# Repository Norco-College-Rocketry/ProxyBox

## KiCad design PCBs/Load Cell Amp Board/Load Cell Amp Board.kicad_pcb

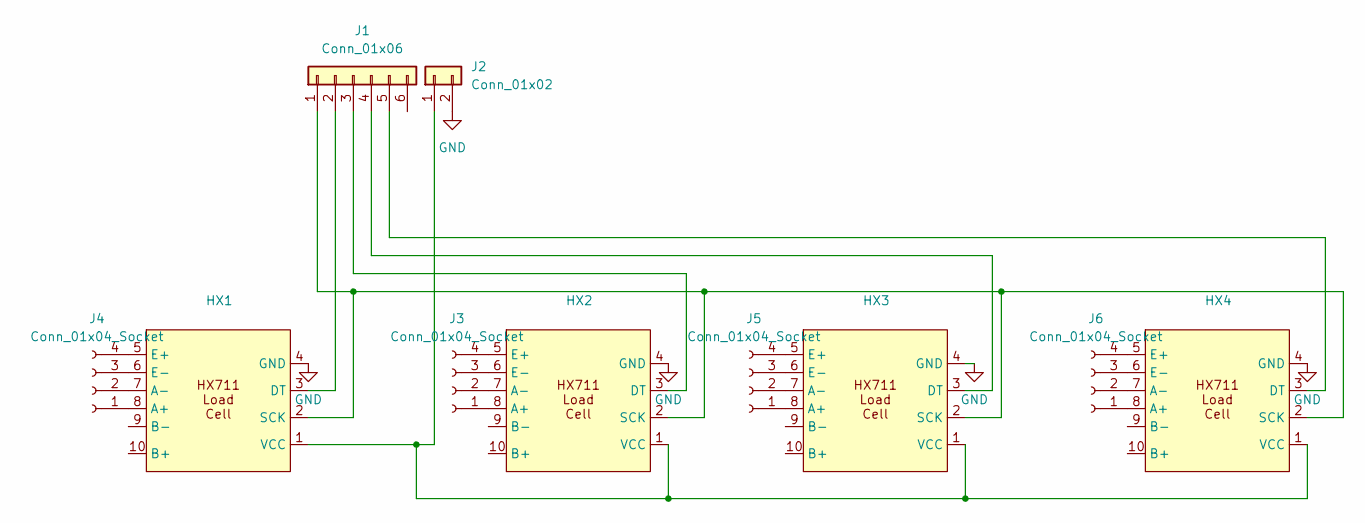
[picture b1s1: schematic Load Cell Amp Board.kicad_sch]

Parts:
HX1, HX2, HX3, HX4: HX711 Load Cell Amp Board
J1: Conn_01x06; Molex_Micro-Fit_3.0_43650-0619_1x06_P3.00mm_Vertical
J2: Conn_01x02; JST_XH_B2B-XH-A_1x02_P2.50mm_Vertical
J3, J4, J5, J6: Conn_01x04_Socket; Molex_Micro-Fit_3.0_43045-0412_2x02_P3.00mm_Vertical

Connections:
GND: HX1.4 (GND), HX2.4 (GND), HX3.4 (GND), HX4.4 (GND), J2.2
unnamed: HX1.8 (A+), J4.1
unnamed: HX1.7 (A-), J4.2
unnamed: HX1.3 (DT), J1.2
unnamed: HX1.5 (E+), J4.4
unnamed: HX1.6 (E-), J4.3
unnamed: HX1.2 (SCK), HX2.2 (SCK), HX3.2 (SCK), HX4.2 (SCK), J1.1
unnamed: HX1.1 (VCC), HX2.1 (VCC), HX3.1 (VCC), HX4.1 (VCC), J2.1
unnamed: HX2.8 (A+), J3.1
unnamed: HX2.7 (A-), J3.2
unnamed: HX2.3 (DT), J1.3
unnamed: HX2.5 (E+), J3.4
unnamed: HX2.6 (E-), J3.3
unnamed: HX3.8 (A+), J5.1
unnamed: HX3.7 (A-), J5.2
unnamed: HX3.3 (DT), J1.4
unnamed: HX3.5 (E+), J5.4
unnamed: HX3.6 (E-), J5.3
unnamed: HX4.8 (A+), J6.1
unnamed: HX4.7 (A-), J6.2
unnamed: HX4.3 (DT), J1.5
unnamed: HX4.5 (E+), J6.4
unnamed: HX4.6 (E-), J6.3

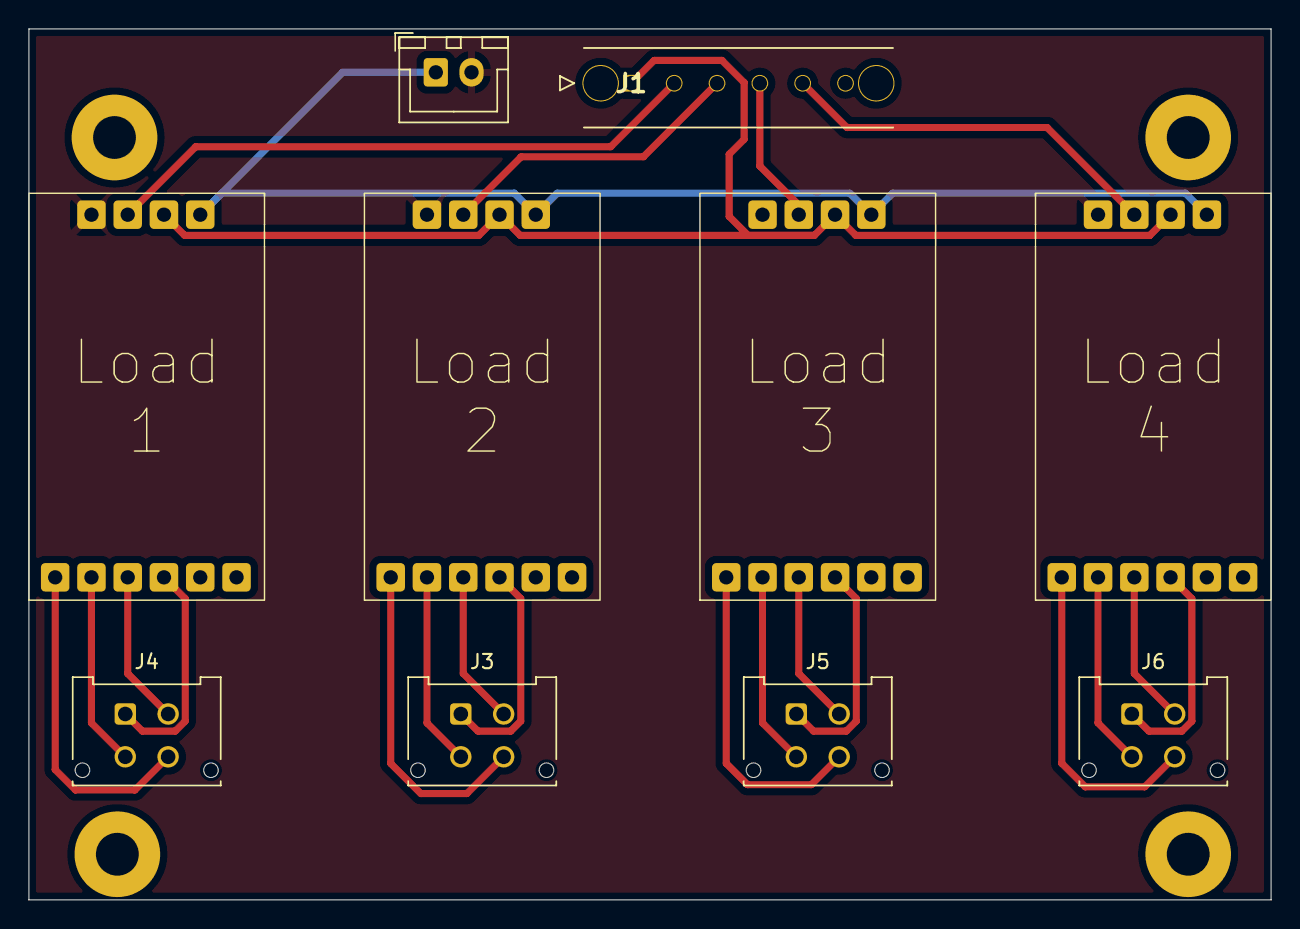
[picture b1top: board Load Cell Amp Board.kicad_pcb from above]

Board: 2 copper layers, 87.0 x 61.0 mm, 10 parts (0 on the bottom side), 23 nets.

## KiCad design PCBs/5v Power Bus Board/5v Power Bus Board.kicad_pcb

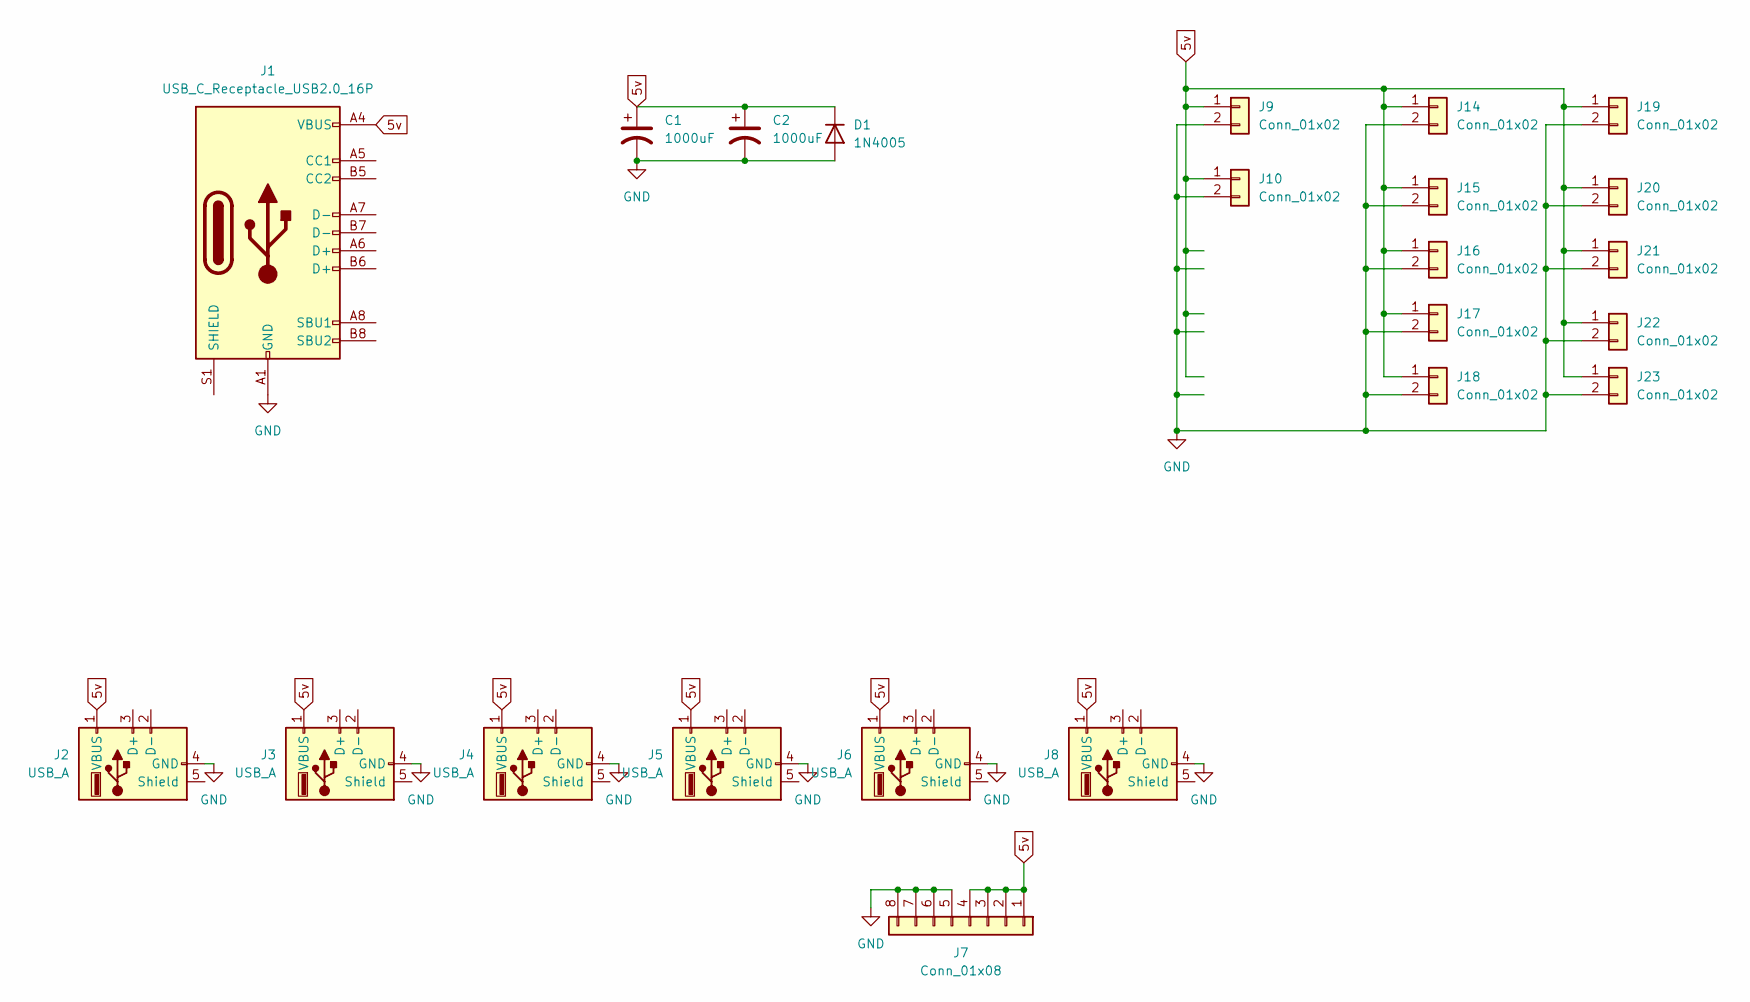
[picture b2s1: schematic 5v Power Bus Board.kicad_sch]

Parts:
C1, C2: 1000uF; CP_Radial_D12.5mm_P5.00mm
D1: 1N4005; D_DO-41_SOD81_P10.16mm_Horizontal
J1: USB_C_Receptacle_USB2.0_16P; USB_C_Receptacle_GCT_USB4105-xx-A_16P_TopMnt_Horizontal
J2, J3, J4, J5, J6, J8: USB_A; USB1125GFB
J7: Conn_01x08; TerminalBlock_4Ucon_1x08_P3.50mm_Horizontal
J9, J10, J14, J15, J16, J17, J18, J19, J20, J21, J22, J23: Conn_01x02; JST_XH_B2B-XH-A_1x02_P2.50mm_Vertical

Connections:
5v: C1.1, C2.1, D1.1 (K), J1.A4 (VBUS), J1.A9 (VBUS), J1.B4 (VBUS), J1.B9 (VBUS), J2.1 (VBUS), J3.1 (VBUS), J4.1 (VBUS), J5.1 (VBUS), J6.1 (VBUS), J7.1, J7.2, J7.3, J7.4, J8.1 (VBUS), J9.1, J10.1, J14.1, J15.1, J16.1, J17.1, J18.1, J19.1, J20.1, J21.1, J22.1, J23.1
GND: C1.2, C2.2, D1.2 (A), J1.A1 (GND), J1.A12 (GND), J1.B1 (GND), J1.B12 (GND), J2.4 (GND), J3.4 (GND), J4.4 (GND), J5.4 (GND), J6.4 (GND), J7.5, J7.6, J7.7, J7.8, J8.4 (GND), J9.2, J10.2, J14.2, J15.2, J16.2, J17.2, J18.2, J19.2, J20.2, J21.2, J22.2, J23.2

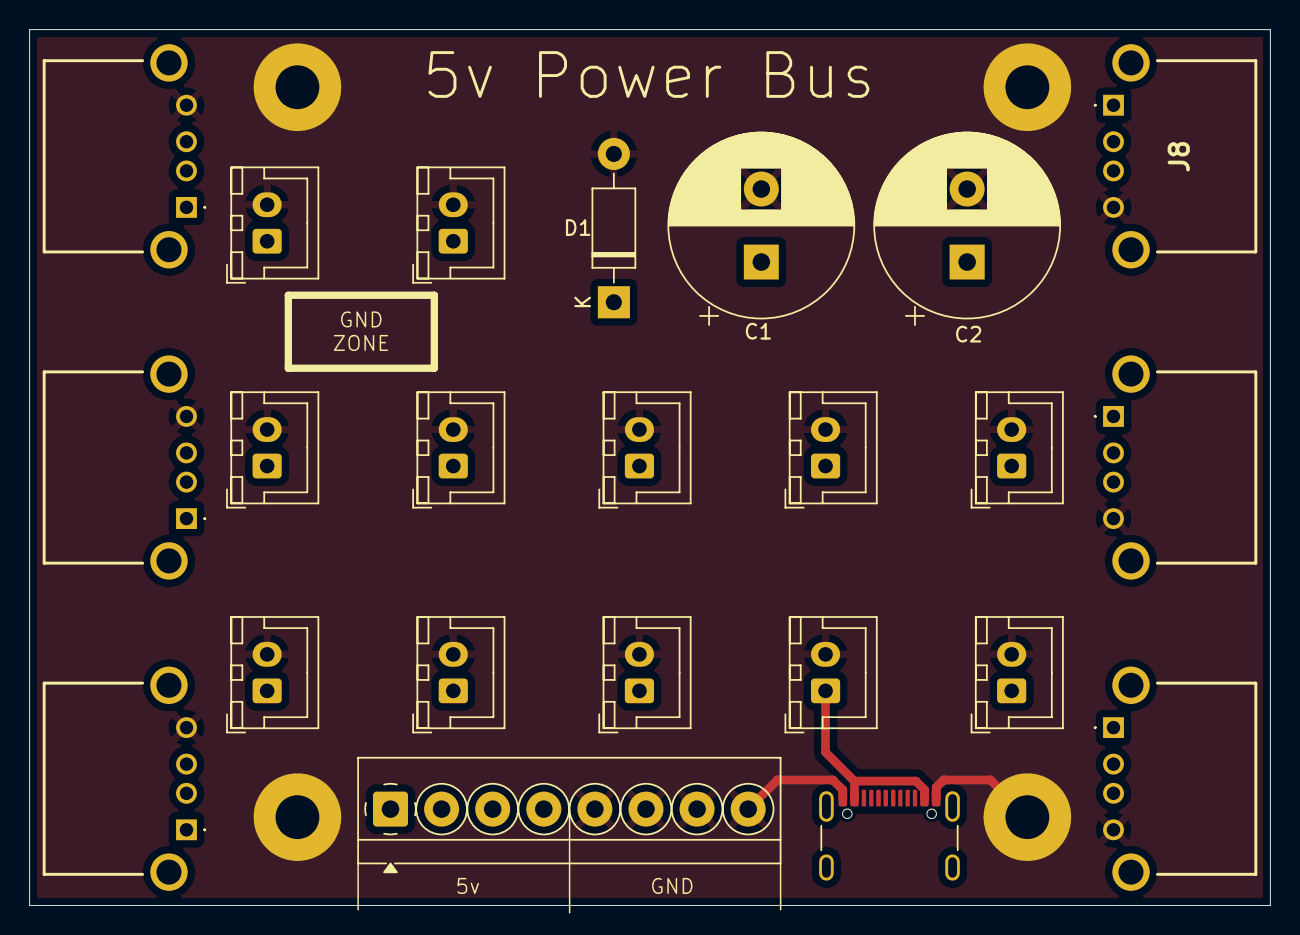
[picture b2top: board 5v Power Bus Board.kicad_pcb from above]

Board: 2 copper layers, 85.0 x 60.0 mm, 23 parts (0 on the bottom side), 2 nets.

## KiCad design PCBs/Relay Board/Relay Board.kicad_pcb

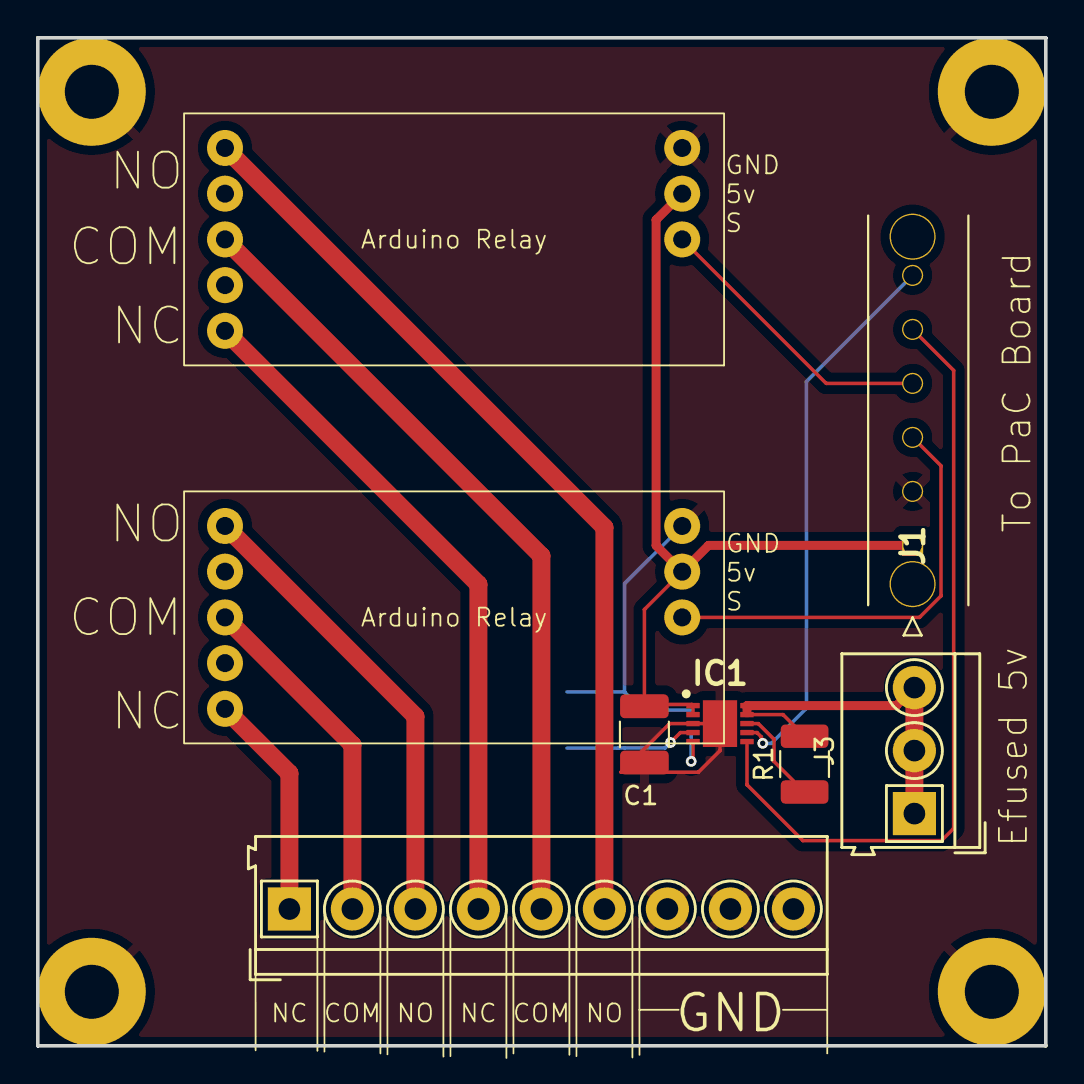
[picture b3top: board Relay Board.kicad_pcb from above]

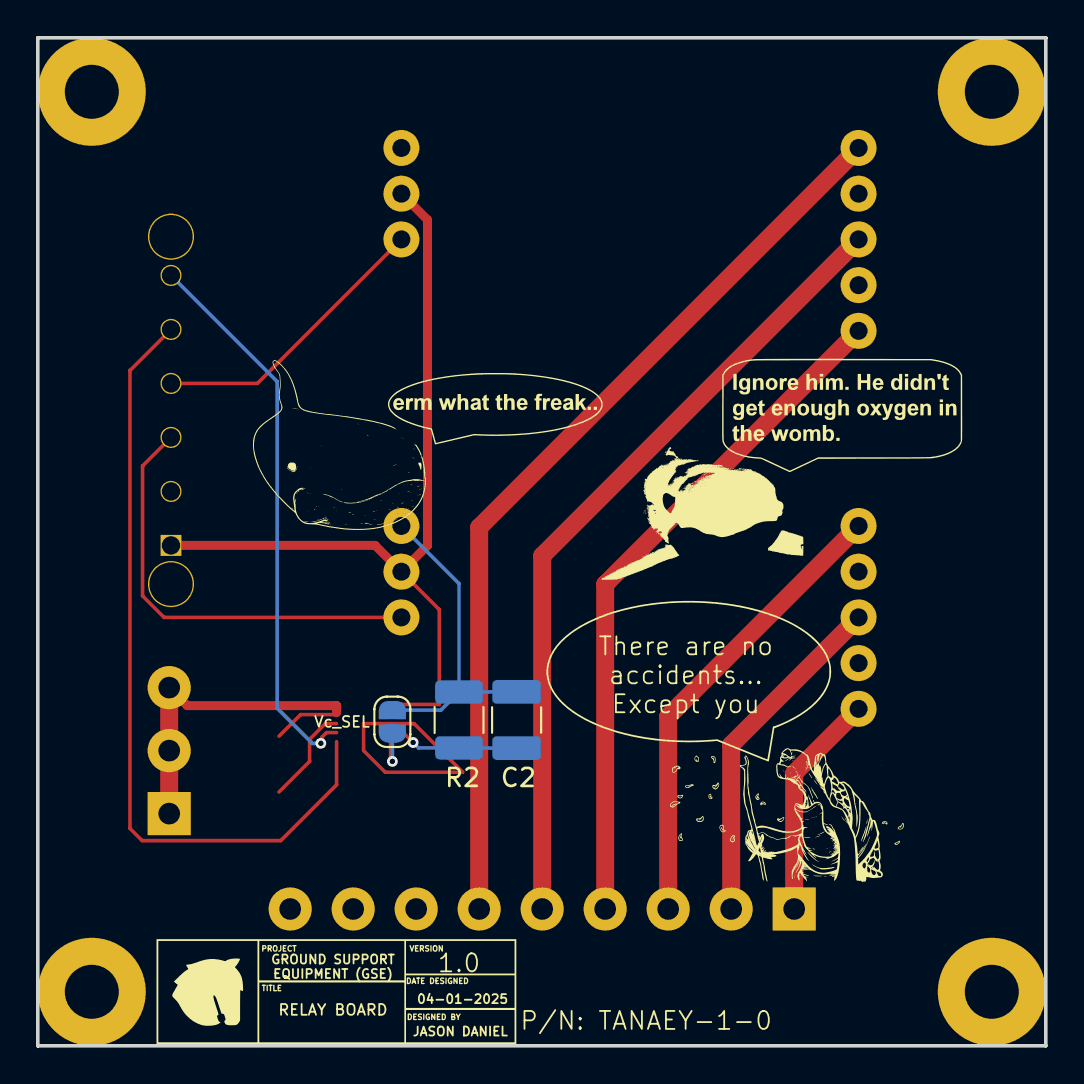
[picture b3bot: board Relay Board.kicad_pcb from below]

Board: 2 copper layers, 56.0 x 56.0 mm, 11 parts (3 on the bottom side), 16 nets.

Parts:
C1: 4.7uF; C_1210_3225Metric_Pad1.33x2.70mm_HandSolder
C2: 1uF; C_1210_3225Metric_Pad1.33x2.70mm_HandSolder
IC1: NIS6150MT1TXG; [NIS6150MT1TXG] Efuse
J1: Conn_01x06; Molex_Micro-Fit_3.0_43650-0619_1x06_P3.00mm_Vertical
J2: Conn_01x09; PCB_Terminal_Block_9_DEG381-3.5
J3: Conn_01x03; PCB_Terminal_Block_3_DEG381-3.5
JP2: SolderJumper_2_Open; SolderJumper-2_P1.3mm_Open_RoundedPad1.0x1.5mm
K1, K2: Arduino_Relay_5v; 5v Arduino Relay
R1: 2ohm; R_1210_3225Metric_Pad1.30x2.65mm_HandSolder
R2: 1kohm; R_1210_3225Metric_Pad1.30x2.65mm_HandSolder

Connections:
5v: C1.1, IC1.1 (VCC_1), IC1.2 (VCC_2), J1.1, K1.2 (5v), K2.2 (5v)
GND: C1.2, C2.2, IC1.3 (GND), IC1.11 (EP), J1.2, J2.7, J2.8, J2.9, JP2.1 (A), K1.3 (Gnd), K2.3 (Gnd), R2.1
unnamed: IC1.7 (EN), J1.6
unnamed: IC1.6 (FLAG), J1.5
unnamed: IC1.8 (ILIM), R1.1
unnamed: C2.1, IC1.4 (IMON), R2.2
unnamed: IC1.9 (SRC_1), IC1.10 (SRC_2), J3.1, J3.2, J3.3, R1.2
unnamed: IC1.5 (VC_SEL), JP2.2 (B)
unnamed: J1.3, K1.1 (Signal)
unnamed: J1.4, K2.1 (Signal)
unnamed: J2.1, K1.6
unnamed: J2.2, K1.5
unnamed: J2.3, K1.4
unnamed: J2.4, K2.6
unnamed: J2.5, K2.5
unnamed: J2.6, K2.4

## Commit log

2025-01-07 Initial commit Read telemetry from CAN bus Blink relays
2025-01-07 Basic Load Cells
2025-01-07 Changed packet type cause i had voltage originally
2025-01-07 Made load cells into a function
2025-01-11 Parse MQTT stream
2025-01-16 Move packet enums to common header
2025-01-16 Add HX711 ADC library to PIO project
2025-01-21 Change return type to float array
2025-01-21 Connect to MQTT before initalizing HX711
2025-01-21 Fix pin assignments
2025-01-21 Send load cell values over MQTT and serial
2025-01-28 Fix type; assert relay 2 low
2025-01-29 Add thermocouple telemetry handling
2025-01-29 Restore PT calibration debug commands
2025-02-02 Remove MQTT debug output
2025-02-02 Refactor load cells
2025-02-02 Pare LoadCell class down to a struct
2025-02-05 Adhere to new telemetry and command packet formats
2025-02-05 Implement valve command
2025-02-05 Set Platform.io serial monitor baud
2025-02-07 Fix valve comand packet Use else-if's instead of if's to parse received command
2025-02-07 Update CAN packet typedefs
2025-02-08 Use valve command packet type define Rename read_float to parse_float
2025-02-12 Extract sending valve command to a function
2025-02-12 Add docstring
2025-02-16 Fix updating load cell amplifiers
2025-02-16 Implement abort sequence
2025-02-16 Publish thrust telemetry
2025-05-06 Update pins for new PCB Update P&ID numbers & MQTT topics Add launch command Retry CAN initialization periodically on startup
2025-05-09 Test LTC2990 with Wire library (broken)
